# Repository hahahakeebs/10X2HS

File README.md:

# 10X2HS

A hotswap variant of [10x2](https://github.com/miketronic/10x2) by [miketronic](https://github.com/miketronic)

# these files are not verified yet, get them printed at your own risk

original readme preserved below

[More pictures here](https://imgur.com/a/LNFxImS)

## Features

- 20 keys
- Low profile choc switches with CFX spacing (closer spacing then standard choc, only caps of size 16.50mm x 16.50mm will fit)
- RGB lighting (not on v3G)
- Waveshare RP2040 Zero controller
- QMK firmware
- [ZMK firmware - module here ](https://github.com/miketronic/zmk-keyboards-10x2/tree/main)

## Introduction

Capsule3 (which I've renamed to 10x2 thanks to the great suggestion by daveurr on Discord) is the third addition to my Capsule series, the first two not being worthy of being posted publicly haha.

The idea for this keyboard (and subsequent keymap) was to design a layout that avoids any lateral finger movement as you would on conventional full-sized keyboards. Moving your fingers only up and down on the columns provides a more enjoyable experience and can reduce or eliminate RSI (repetitve strain injury) in your fingers.

But how only 18 total letter keys? By building a custom firmware layout and using combos for less used letters, or where they "feel best". I performed some studies on letter frequency in the English language and most common bigrams and trigrams to determind the layout.

## Keycaps

As noted in the _Features_, I chose a narrower keyswitch spacing and thus they require narrower keycaps. CFX keycaps are commercially available from Chosfox, or you can print your own, for which I've included files. They easily print upside down on an FDM printer, and I use a textured baseplate.

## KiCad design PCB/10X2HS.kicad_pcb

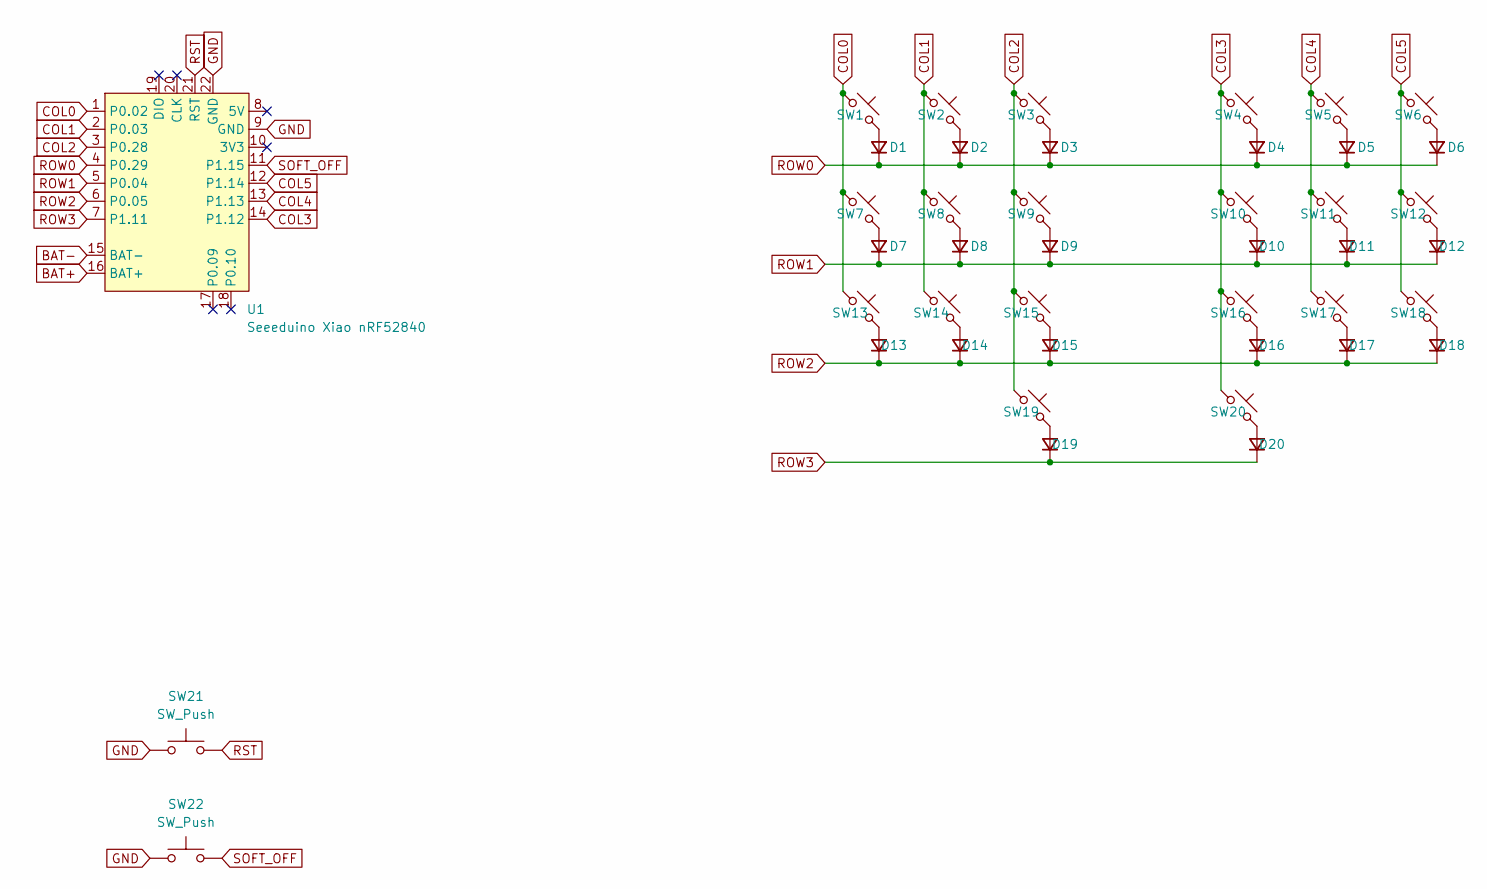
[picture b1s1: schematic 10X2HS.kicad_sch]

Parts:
D1, D2, D3, D4, D5, D6, D7, D8, D9, D10, D11, D12, D13, D14, D15, D16, D17, D18, D19, D20: 1n4148; D_SOD-123
SW1, SW2, SW3, SW4, SW5, SW6, SW7, SW8, SW9, SW10, SW11, SW12, SW13, SW14, SW15, SW16, SW17, SW18, SW19, SW20: MX_SW_solder; SW_MX_1u_rev
SW21, SW22: SW_Push; SW_PUSH_6mm
U1: Seeeduino Xiao nRF52840; Xiao_nRF52840_ACH

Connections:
BAT+: U1.16 (BAT+)
BAT-: U1.15 (BAT-)
COL0: SW1.1, SW7.1, SW13.1, U1.1 (P0.02)
COL1: SW2.1, SW8.1, SW14.1, U1.2 (P0.03)
COL2: SW3.1, SW9.1, SW15.1, SW19.1, U1.3 (P0.28)
COL3: SW4.1, SW10.1, SW16.1, SW20.1, U1.14 (P1.12)
COL4: SW5.1, SW11.1, SW17.1, U1.13 (P1.13)
COL5: SW6.1, SW12.1, SW18.1, U1.12 (P1.14)
GND: SW21.1, SW22.1, U1.9 (GND), U1.22 (GND)
unnamed: D1.2 (A), SW1.2
unnamed: D2.2 (A), SW2.2
unnamed: D3.2 (A), SW3.2
unnamed: D4.2 (A), SW4.2
unnamed: D5.2 (A), SW5.2
unnamed: D6.2 (A), SW6.2
unnamed: D7.2 (A), SW7.2
unnamed: D8.2 (A), SW8.2
unnamed: D9.2 (A), SW9.2
unnamed: D10.2 (A), SW10.2
unnamed: D11.2 (A), SW11.2
unnamed: D12.2 (A), SW12.2
unnamed: D13.2 (A), SW13.2
unnamed: D14.2 (A), SW14.2
unnamed: D15.2 (A), SW15.2
unnamed: D16.2 (A), SW16.2
unnamed: D17.2 (A), SW17.2
unnamed: D18.2 (A), SW18.2
unnamed: D19.2 (A), SW19.2
unnamed: D20.2 (A), SW20.2
ROW0: D1.1 (K), D2.1 (K), D3.1 (K), D4.1 (K), D5.1 (K), D6.1 (K), U1.4 (P0.29)
ROW1: D7.1 (K), D8.1 (K), D9.1 (K), D10.1 (K), D11.1 (K), D12.1 (K), U1.5 (P0.04)
ROW2: D13.1 (K), D14.1 (K), D15.1 (K), D16.1 (K), D17.1 (K), D18.1 (K), U1.6 (P0.05)
ROW3: D19.1 (K), D20.1 (K), U1.7 (P1.11)
RST: SW21.2, U1.21 (RST)
SOFT_OFF: SW22.2, U1.11 (P1.15)

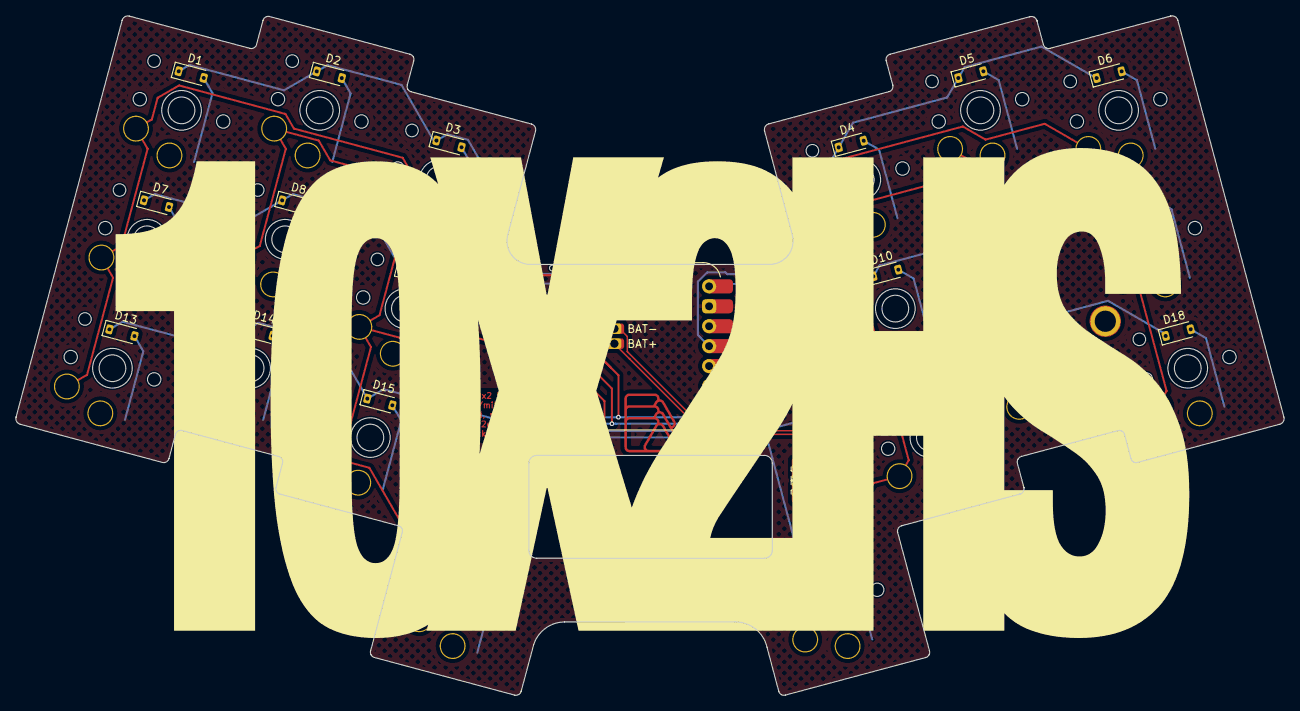
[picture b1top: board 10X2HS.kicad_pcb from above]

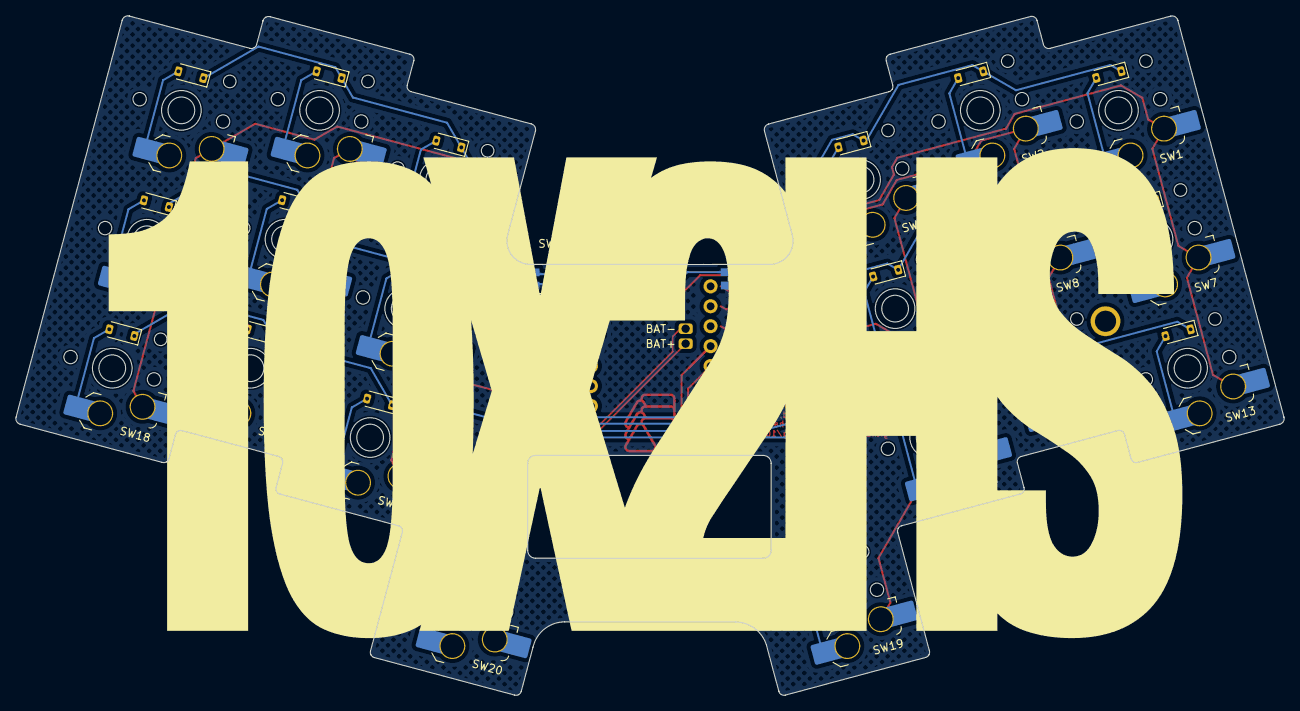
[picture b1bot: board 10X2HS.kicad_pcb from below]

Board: 2 copper layers, 161.5 x 86.5 mm, 50 parts (22 on the bottom side), 33 nets.

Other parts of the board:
H01, H02, H03, H04, H05, H06, H07: M2 Solder Nut; M2_Solder_nut_small_HS

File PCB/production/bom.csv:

Designator,Footprint,Quantity,Value,LCSC Part #
"D1, D10, D11, D12, D13, D14, D15, D16, D17, D18, D19, D2, D20, D3, D4, D5, D6, D7, D8, D9",D_SOD-123,20,1n4148,
"H01, H02, H03, H04, H05, H06, H07",M2_Solder_nut_small_HS,7,M2 Solder Nut,C3020123
"SW1, SW10, SW11, SW12, SW13, SW14, SW15, SW16, SW17, SW18, SW19, SW2, SW20, SW3, SW4, SW5, SW6, SW7, SW8, SW9",choc hs v1v2 led,20,MX_SW_solder,
"SW21, SW22",Panasonic_EVQPUL_EVQPUC,2,SW_Push,

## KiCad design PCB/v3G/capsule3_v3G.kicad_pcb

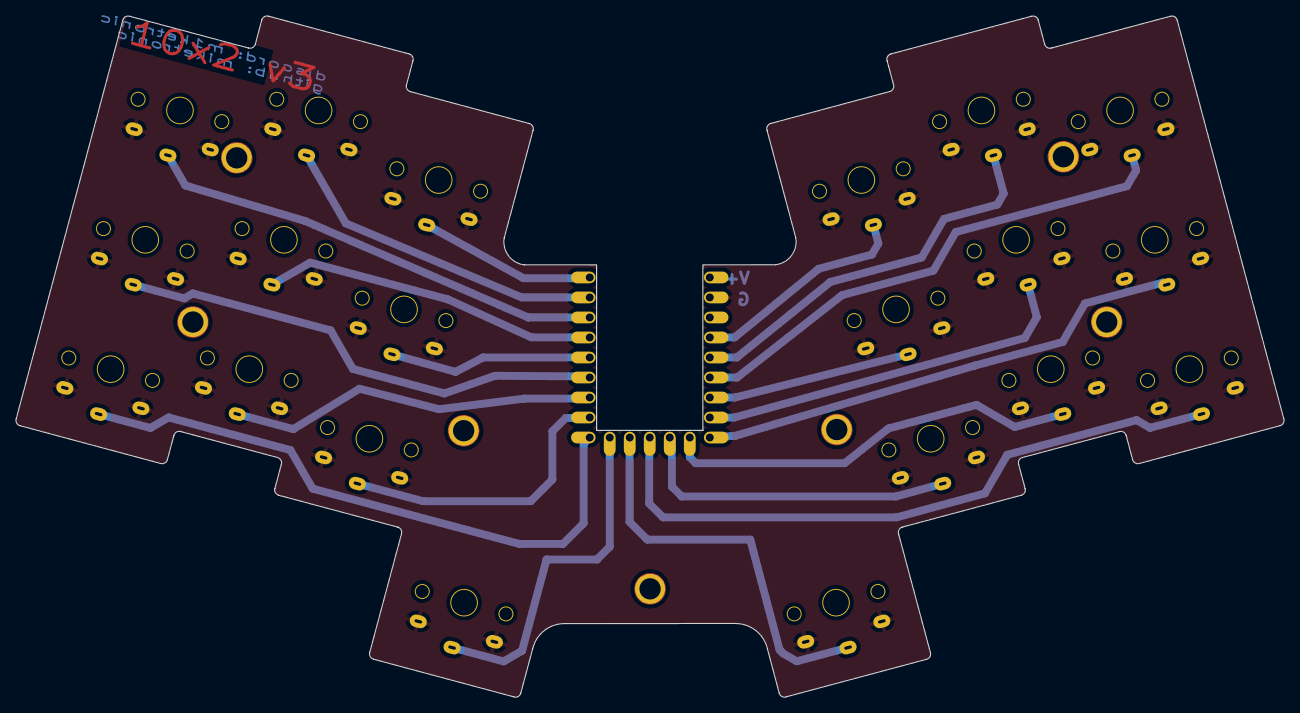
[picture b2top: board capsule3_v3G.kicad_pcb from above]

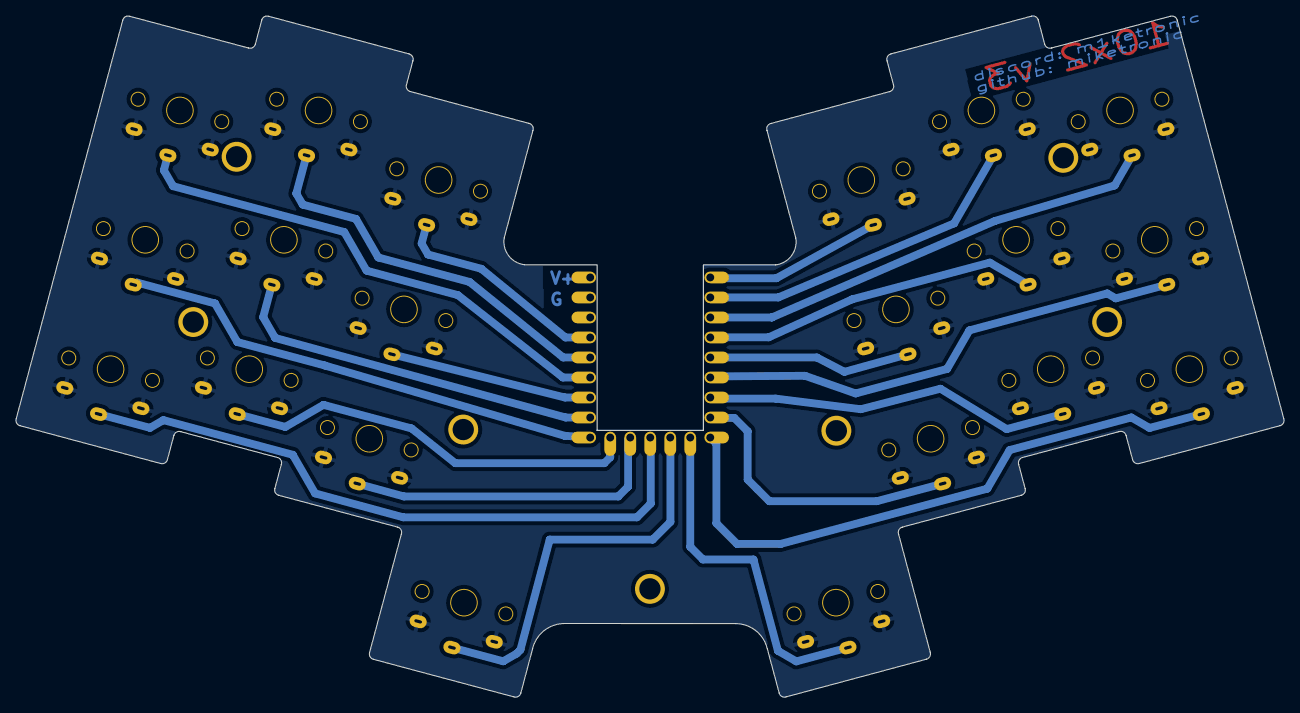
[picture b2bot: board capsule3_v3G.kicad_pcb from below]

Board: 2 copper layers, 160.9 x 86.4 mm, 28 parts (21 on the bottom side), 21 nets.

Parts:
H01, H02, H03, H04, H05, H06, H07: M2 Solder Nut; M2_Solder_nut_small_HS
SW01, SW02, SW03, SW04, SW05, SW06, SW07, SW08, SW09, SW10, SW11, SW12, SW13, SW14, SW15, SW16, SW17, SW18, SW19, SW20: SW; MB_KailhChoc-1U_rev_17mm_oval
U1: rp2040-zero; MB_rp2040-zero-tht

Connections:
GND: SW01.2, SW02.2, SW03.2, SW04.2, SW05.2, SW06.2, SW07.2, SW08.2, SW09.2, SW10.2, SW11.2, SW12.2, SW13.2, SW14.2, SW15.2, SW16.2, SW17.2, SW18.2, SW19.2, SW20.2, U1.22 (GND)
SW01: SW01.1, U1.3 (2)
SW02: SW02.1, U1.2 (1)
SW03: SW03.1, U1.1 (0)
SW04: SW04.1, U1.20 (29)
SW05: SW05.1, U1.19 (28)
SW06: SW06.1, U1.18 (27)
SW07: SW07.1, U1.6 (5)
SW08: SW08.1, U1.4 (3)
SW09: SW09.1, U1.5 (4)
SW10: SW10.1, U1.17 (26)
SW11: SW11.1, U1.16 (15)
SW12: SW12.1, U1.15 (14)
SW13: SW13.1, U1.9 (8)
SW14: SW14.1, U1.7 (6)
SW15: SW15.1, U1.8 (7)
SW16: SW16.1, U1.13 (12)
SW17: SW17.1, U1.14 (13)
SW18: SW18.1, U1.12 (11)
SW19: SW19.1, U1.10 (9)
SW20: SW20.1, U1.11 (10)

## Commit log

2024-04-04 Rename readme.txt to readme.md
2024-12-09 Create keep
2025-06-17 maybe complete, cleanup still needs done
2025-06-17 readme skeleton
2025-07-22 protos ordered, case designed, v.1 complete
2025-07-22 more updates I guess
2025-08-03 backups
2025-08-25 firmware
2025-08-25 json for zmkke
2025-12-12 changed to nonplus xiao, add direct battery pads

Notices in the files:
README.md:
License: CC BY-SA 4.0
